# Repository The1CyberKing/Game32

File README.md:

### The goal:

Show CSS 342 Knowledge with C++

Show new learning of ESP32 as a beginner.

Showcase skills of building firmware, not the games. Specifically the firmware to allows for Arduboy games to run on Game32 (why reinvent the wheel? Compare to How firmware is built to run windows. Allat stuff)

Since hardware selection is low risk, we started with a hardware first solution (Hardware first development). Finished the hardware before coding.

As lazy as it sounds I didnt want to open my phone when gaming, so esp32 was the way to go

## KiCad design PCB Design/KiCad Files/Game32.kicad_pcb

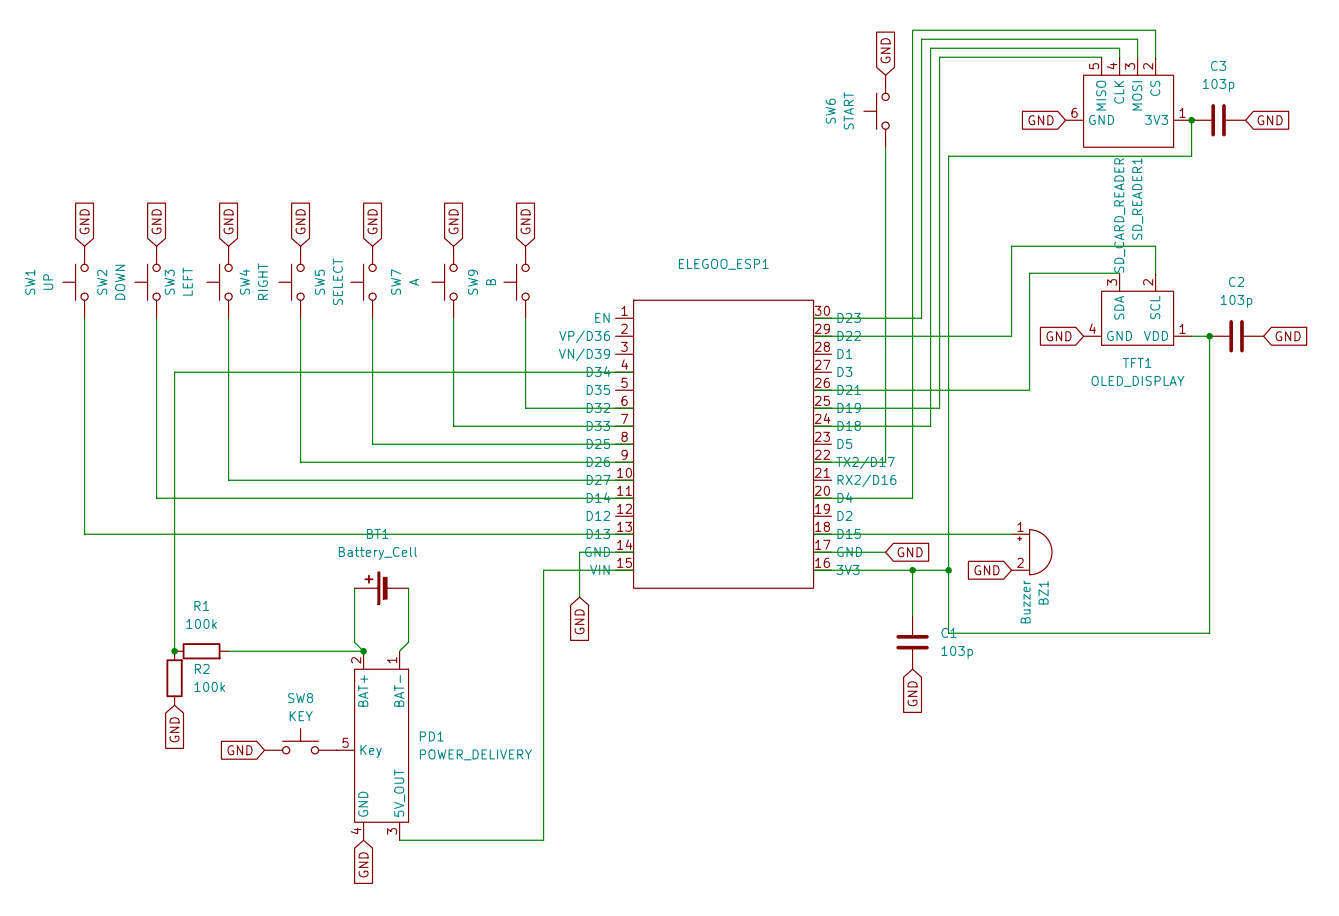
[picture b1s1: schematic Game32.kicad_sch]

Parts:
BT1: Battery_Cell; 2_Battery_Pads
BZ1: Buzzer; Buzzer_TH_7mm_2Pin
C1, C2, C3: 103p; C_0805_2012Metric; LCSC C1710
ELEGOO_ESP1: ELEGOO ESP32 DevKit Type C V1
PD1: POWER_DELIVERY; 5V_Boost_Converter
R1, R2: 100k; R_0805_2012Metric; LCSC C149504
SD_READER1: SD_CARD_READER; SD_Card_Reader_Custom
SW1: UP; SW_Tact_2Pin_6x6x5mm
SW2: DOWN; SW_Tact_2Pin_6x6x5mm
SW3: LEFT; SW_Tact_2Pin_6x6x5mm
SW4: RIGHT; SW_Tact_2Pin_6x6x5mm
SW5: SELECT; SW_Tact_2Pin_6x6x5mm
SW6: START; SW_Tact_2Pin_6x6x5mm
SW7: A; SW_Tact_2Pin_6x6x5mm
SW8: KEY; SW_Tact_2Pin_6x6x5mm
SW9: B; SW_Tact_2Pin_6x6x5mm
TFT1: OLED_DISPLAY; YELUFT-SSD1309-2.42in

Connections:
GND: BZ1.2 (-), C1.1, C2.2, C3.2, ELEGOO_ESP1.14 (GND), ELEGOO_ESP1.17 (GND), PD1.4 (GND), R2.1, SD_READER1.6 (GND), SW1.2, SW2.2, SW3.2, SW4.2, SW5.2, SW6.2, SW7.2, SW8.1, SW9.2, TFT1.4 (GND)
unnamed: BT1.1 (+), PD1.2 (BAT+), R1.2
unnamed: BT1.2 (-), PD1.1 (BAT-)
unnamed: BZ1.1 (+), ELEGOO_ESP1.18 (D15)
unnamed: C1.2, C2.1, C3.1, ELEGOO_ESP1.16 (3V3), SD_READER1.1 (3V3), TFT1.1 (VDD)
unnamed: ELEGOO_ESP1.20 (D4), SD_READER1.2 (CS)
unnamed: ELEGOO_ESP1.13 (D13), SW1.1
unnamed: ELEGOO_ESP1.11 (D14), SW2.1
unnamed: ELEGOO_ESP1.24 (D18), SD_READER1.4 (CLK)
unnamed: ELEGOO_ESP1.25 (D19), SD_READER1.5 (MISO)
unnamed: ELEGOO_ESP1.26 (D21), TFT1.3 (SDA)
unnamed: ELEGOO_ESP1.29 (D22), TFT1.2 (SCL)
unnamed: ELEGOO_ESP1.30 (D23), SD_READER1.3 (MOSI)
unnamed: ELEGOO_ESP1.8 (D25), SW5.1
unnamed: ELEGOO_ESP1.9 (D26), SW4.1
unnamed: ELEGOO_ESP1.10 (D27), SW3.1
unnamed: ELEGOO_ESP1.6 (D32), SW9.1
unnamed: ELEGOO_ESP1.7 (D33), SW7.1
unnamed: ELEGOO_ESP1.4 (D34), R1.1, R2.2
unnamed: ELEGOO_ESP1.22 (TX2/D17), SW6.1
unnamed: ELEGOO_ESP1.15 (VIN), PD1.3 (5V_OUT)
unnamed: PD1.5 (Key), SW8.2

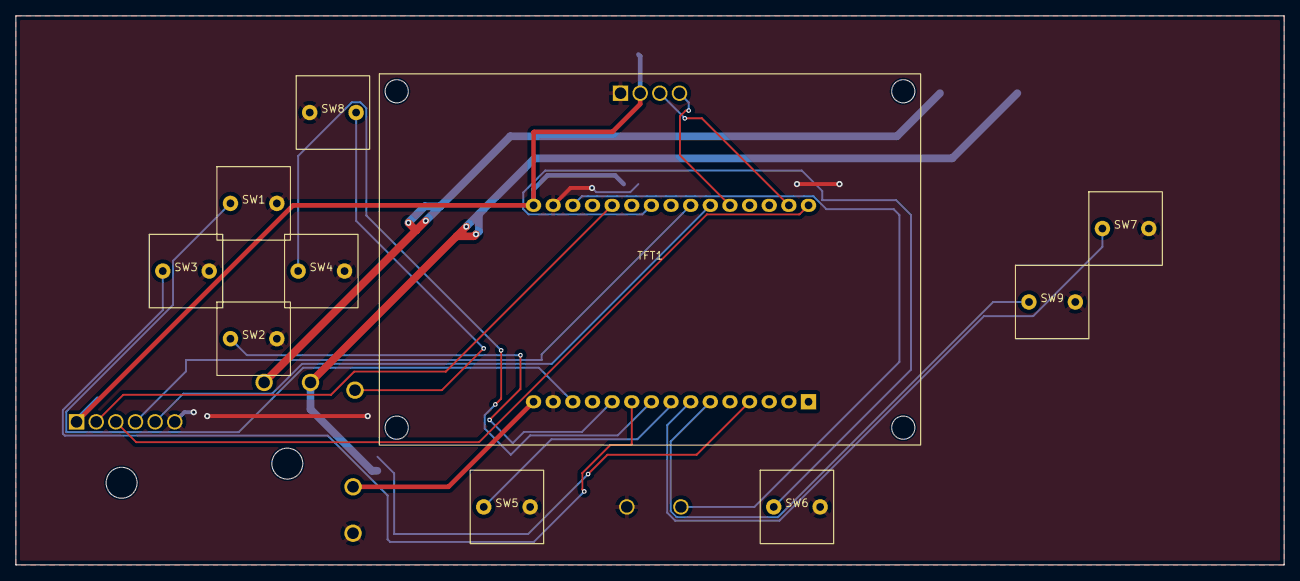
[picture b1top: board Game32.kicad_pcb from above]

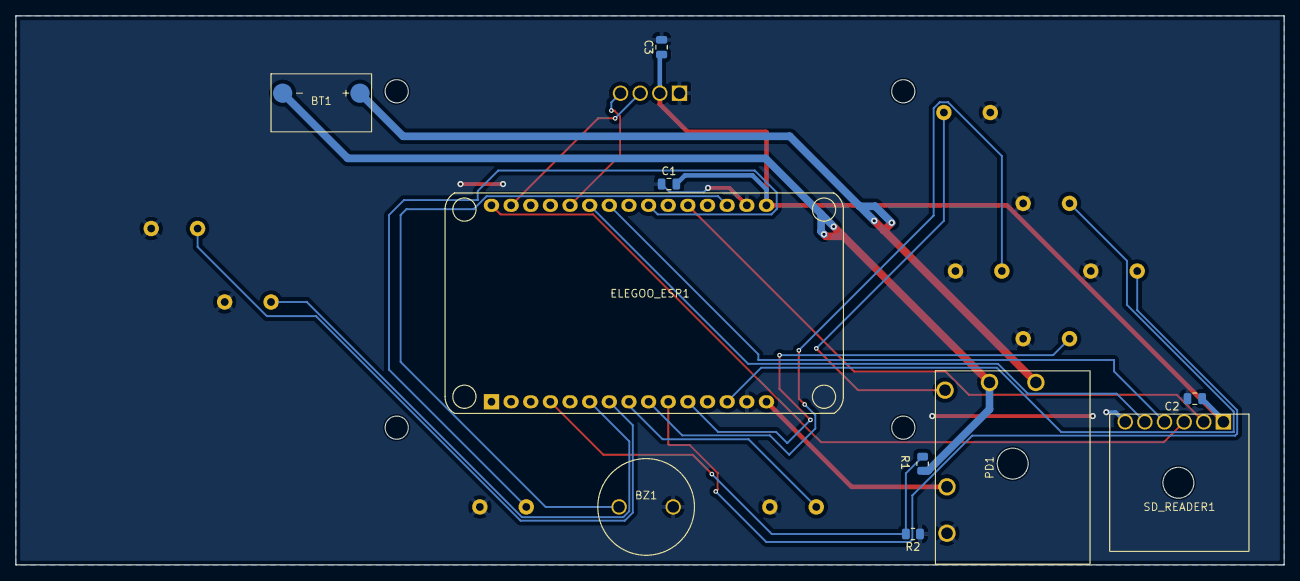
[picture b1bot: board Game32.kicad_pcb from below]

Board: 2 copper layers, 164.0 x 71.0 mm, 20 parts (10 on the bottom side), 22 nets.

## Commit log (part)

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2025-12-28 Initial Commit (Contains Hardware Testing Code)
2026-01-01 Updating the KiCad Files and Wiring Diagram Versions
2026-01-01 Updated PCB designs
2026-03-28 PCB Completed
2026-04-20 Created Boost Converter Fix File
2026-05-24 Version 1 of the 3D Models are Created, to be printed
2026-05-25 Initialization code written, Dry run next
2026-05-25 Fixing Compiling issues (Broken paths)
2026-05-25 Working Boot Page, Display Manager Further Optimized. Flashed to ESP32, Real time Battery Sensing works.
2026-05-26 basic Menu Functionality
2026-05-26 Full Menu Implementation
2026-05-26 Finalized version 1 of the menu state
2026-05-27 Game UI Loads, but Low FPS. Pivoting to User PC Transcompiler
2026-06-12 Prepping for new branch/new Idea
2026-06-27 Clean slate: Wiped emulator core, restored config.h, migrated to ESP-IDF 6.0 APIs, deleted mock_env
    - Removed mock_env/ desktop test environment
    - Wiped EmulatorState to clean stub (kept IGameState interface)
    - Restored include/config.h from main branch
    - Migrated BatteryManager to modern esp_adc/adc_oneshot.h API
    - Fixed DisplayManager GPIO casts for ESP-IDF 6.0
    - Fixed SDManager struct initializer warnings
